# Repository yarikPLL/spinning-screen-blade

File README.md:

# spinning-screen-blade
Designed a blade for spinning screen for science club "SKN MOS" at WUST

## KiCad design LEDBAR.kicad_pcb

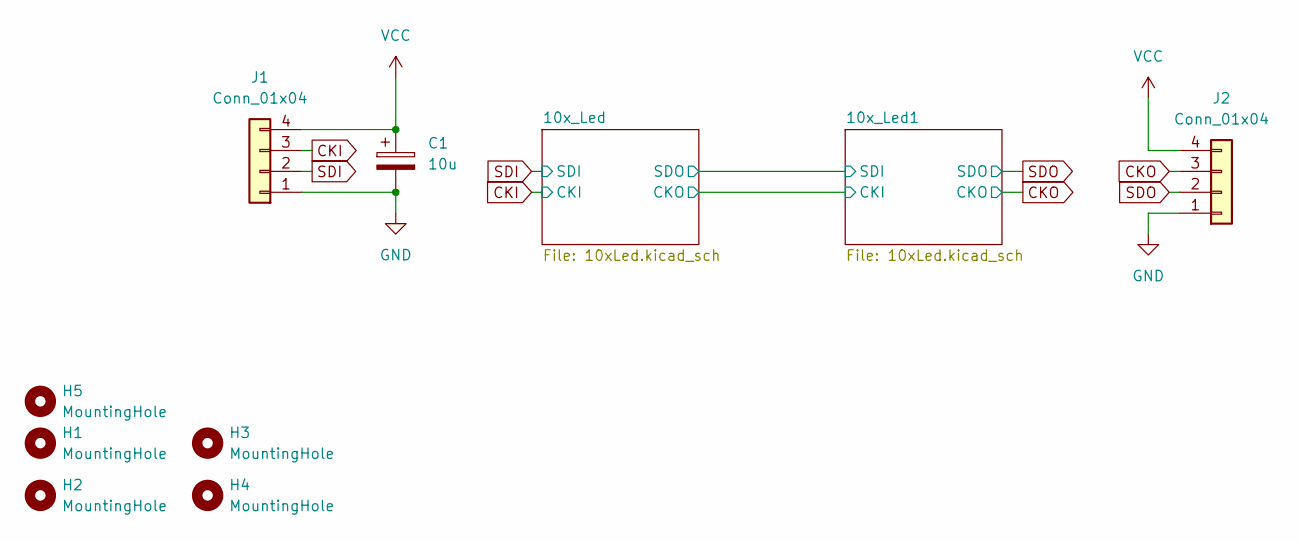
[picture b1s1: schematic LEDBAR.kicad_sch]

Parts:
C1: 10u; CP_Elec_4x5.4
H1, H2, H3, H4: MountingHole; MountingHole_2.2mm_M2_ISO7380
H5: MountingHole; mos
J1: Conn_01x04; PinHeader_1x04_P2.54mm_Horizontal
J2: Conn_01x04; PinHeader_1x04_P2.54mm_Horizontal_1

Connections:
CKI: J1.3; also elsewhere on the board
CKO: J2.3; also elsewhere on the board
GND: C1.2, J1.1, J2.1; also elsewhere on the board
SDI: J1.2; also elsewhere on the board
SDO: J2.2; also elsewhere on the board
VCC: C1.1, J1.4, J2.4; also elsewhere on the board

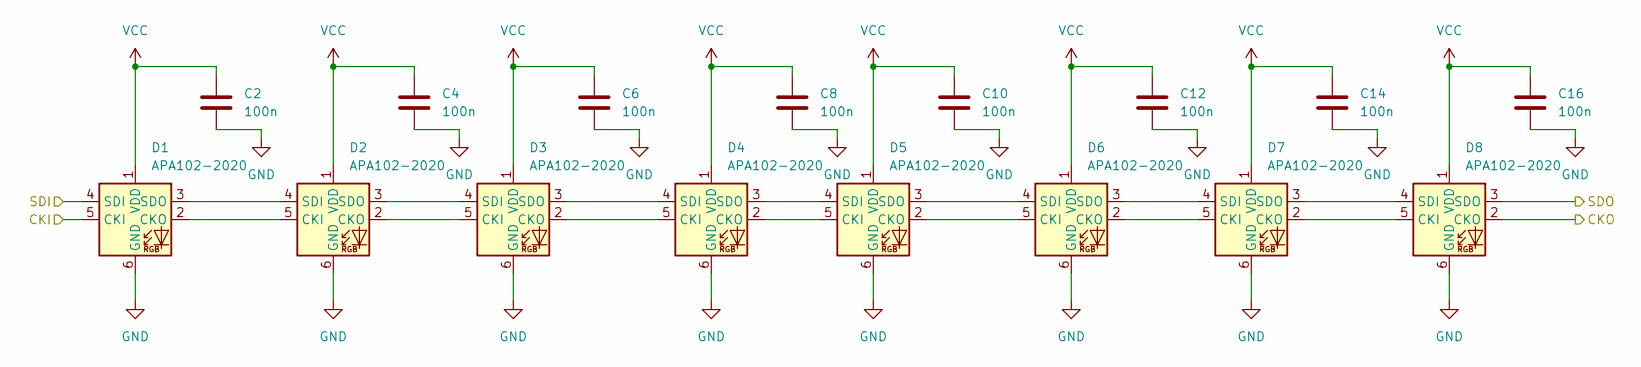
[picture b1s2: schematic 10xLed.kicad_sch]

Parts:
C2, C4, C6, C8, C10, C12, C14, C16: 100n; C_0402_1005Metric_Pad0.74x0.62mm_HandSolder
D1, D2, D3, D4, D5, D6, D7, D8: APA102-2020; LED-APA102-2020

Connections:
/10x_Led/CKO: D8.2 (CKO); also elsewhere on the board
/10x_Led/SDO: D8.3 (SDO); also elsewhere on the board
CKI: D1.5 (CKI); also elsewhere on the board
GND: C2.2, C4.2, C6.2, C8.2, C10.2, C12.2, C14.2, C16.2, D1.6 (GND), D2.6 (GND), D3.6 (GND), D4.6 (GND), D5.6 (GND), D6.6 (GND), D7.6 (GND), D8.6 (GND); also elsewhere on the board
unnamed: D1.2 (CKO), D2.5 (CKI)
unnamed: D1.3 (SDO), D2.4 (SDI)
unnamed: D2.2 (CKO), D3.5 (CKI)
unnamed: D2.3 (SDO), D3.4 (SDI)
unnamed: D3.2 (CKO), D4.5 (CKI)
unnamed: D3.3 (SDO), D4.4 (SDI)
unnamed: D4.2 (CKO), D5.5 (CKI)
unnamed: D4.3 (SDO), D5.4 (SDI)
unnamed: D5.2 (CKO), D6.5 (CKI)
unnamed: D5.3 (SDO), D6.4 (SDI)
unnamed: D6.2 (CKO), D7.5 (CKI)
unnamed: D6.3 (SDO), D7.4 (SDI)
unnamed: D7.2 (CKO), D8.5 (CKI)
unnamed: D7.3 (SDO), D8.4 (SDI)
SDI: D1.4 (SDI); also elsewhere on the board
VCC: C2.1, C4.1, C6.1, C8.1, C10.1, C12.1, C14.1, C16.1, D1.1 (VDD), D2.1 (VDD), D3.1 (VDD), D4.1 (VDD), D5.1 (VDD), D6.1 (VDD), D7.1 (VDD), D8.1 (VDD); also elsewhere on the board

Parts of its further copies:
C3, C5, C7, C9, C11, C13, C15, C17: 100n; C_0402_1005Metric_Pad0.74x0.62mm_HandSolder
D9, D10, D11, D12, D13, D14, D15, D16: APA102-2020; LED-APA102-2020

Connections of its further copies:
/10x_Led/CKO: D9.5 (CKI); also elsewhere on the board
/10x_Led/SDO: D9.4 (SDI); also elsewhere on the board
CKO: D16.2 (CKO); also elsewhere on the board
GND: C3.2, C5.2, C7.2, C9.2, C11.2, C13.2, C15.2, C17.2, D9.6 (GND), D10.6 (GND), D11.6 (GND), D12.6 (GND), D13.6 (GND), D14.6 (GND), D15.6 (GND), D16.6 (GND); also elsewhere on the board
unnamed: D9.2 (CKO), D10.5 (CKI)
unnamed: D10.2 (CKO), D11.5 (CKI)
unnamed: D9.3 (SDO), D10.4 (SDI)
unnamed: D10.3 (SDO), D11.4 (SDI)
unnamed: D11.2 (CKO), D12.5 (CKI)
unnamed: D11.3 (SDO), D12.4 (SDI)
unnamed: D12.2 (CKO), D13.5 (CKI)
unnamed: D12.3 (SDO), D13.4 (SDI)
unnamed: D13.2 (CKO), D14.5 (CKI)
unnamed: D13.3 (SDO), D14.4 (SDI)
unnamed: D14.2 (CKO), D15.5 (CKI)
unnamed: D14.3 (SDO), D15.4 (SDI)
unnamed: D15.2 (CKO), D16.5 (CKI)
unnamed: D15.3 (SDO), D16.4 (SDI)
SDO: D16.3 (SDO); also elsewhere on the board
VCC: C3.1, C5.1, C7.1, C9.1, C11.1, C13.1, C15.1, C17.1, D9.1 (VDD), D10.1 (VDD), D11.1 (VDD), D12.1 (VDD), D13.1 (VDD), D14.1 (VDD), D15.1 (VDD), D16.1 (VDD); also elsewhere on the board

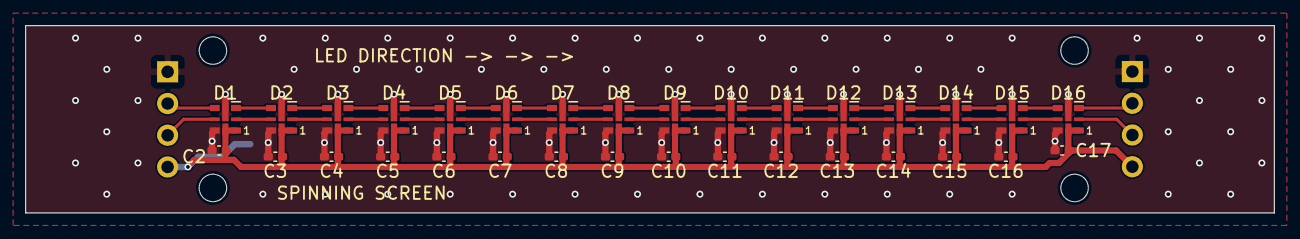
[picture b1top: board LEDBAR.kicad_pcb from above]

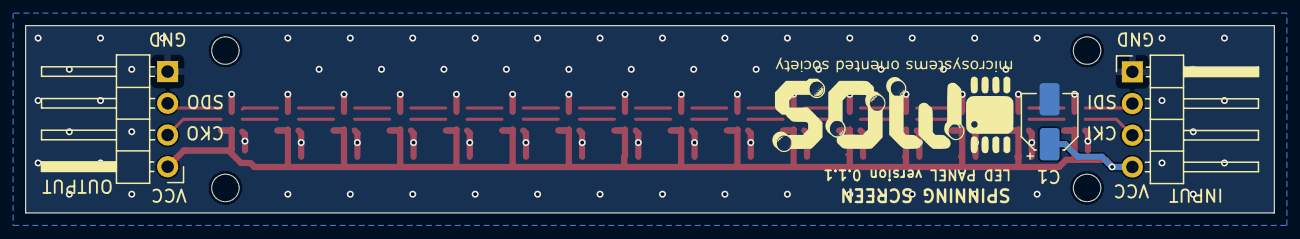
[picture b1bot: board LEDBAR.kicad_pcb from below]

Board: 2 copper layers, 100.0 x 15.0 mm, 40 parts (4 on the bottom side), 36 nets.

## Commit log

2025-09-14 added my project to repository
2025-09-14 repo cleanup
